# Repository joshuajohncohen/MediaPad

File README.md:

# MediaPad
A macropad for controlling media playback (For Highway)

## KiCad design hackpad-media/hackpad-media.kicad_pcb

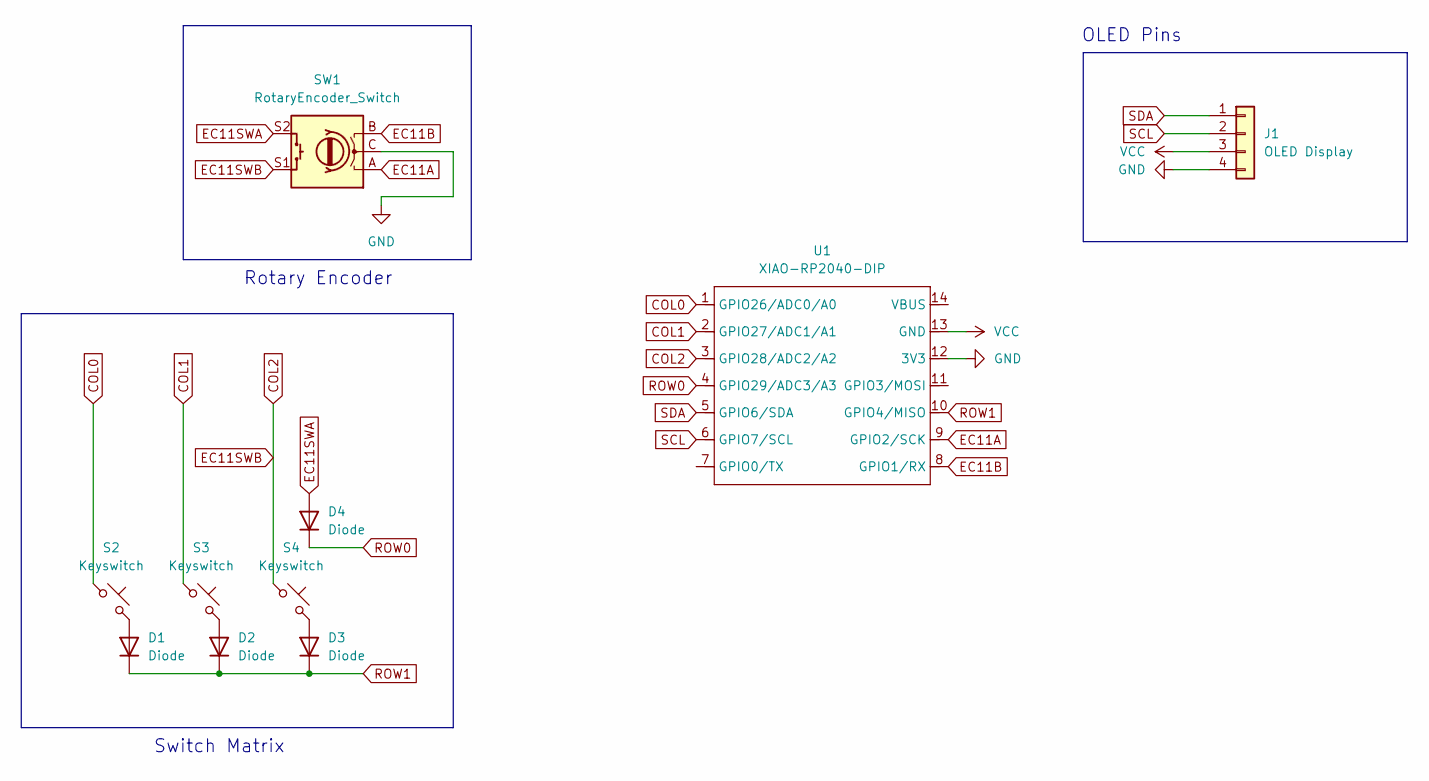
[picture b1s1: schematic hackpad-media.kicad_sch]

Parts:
D1, D2, D3, D4: Diode; Diode_DO-35
J1: OLED Display; OLED_128x32
S2, S3, S4: Keyswitch; MX_PCB_1.00u
SW1: RotaryEncoder_Switch; RotaryEncoder_Alps_EC11E-Switch_Vertical_H20mm_CircularMoun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
U1: XIAO-RP2040-DIP; XIAO-RP2040-DIP-3D

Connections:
COL0: S2.1, U1.1 (GPIO26/ADC0/A0)
COL1: S3.1, U1.2 (GPIO27/ADC1/A1)
COL2: S4.1, SW1.S1, U1.3 (GPIO28/ADC2/A2)
EC11A: SW1.A, U1.9 (GPIO2/SCK)
EC11B: SW1.B, U1.8 (GPIO1/RX)
EC11SWA: D4.2 (A), SW1.S2
GND: J1.4 (GND), SW1.C, U1.12 (3V3)
unnamed: D1.2 (A), S2.2
unnamed: D2.2 (A), S3.2
unnamed: D3.2 (A), S4.2
ROW0: D4.1 (K), U1.4 (GPIO29/ADC3/A3)
ROW1: D1.1 (K), D2.1 (K), D3.1 (K), U1.10 (GPIO4/MISO)
SCL: J1.2 (SCL), U1.6 (GPIO7/SCL)
SDA: J1.1 (SDA), U1.5 (GPIO6/SDA)
VCC: J1.3 (VCC), U1.13 (GND)

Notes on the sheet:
OLED Pins
Rotary Encoder
Switch Matrix

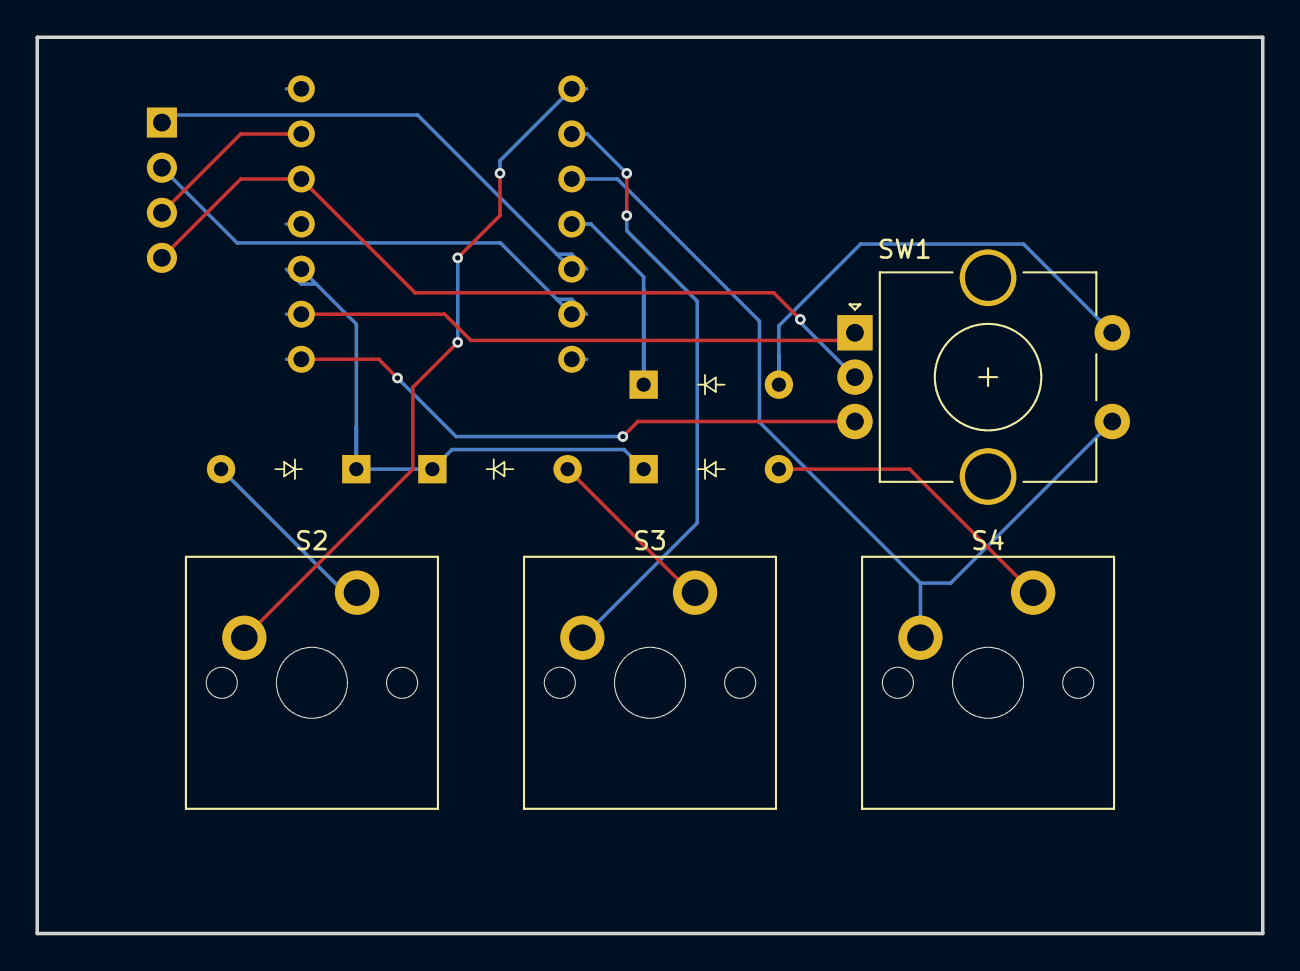
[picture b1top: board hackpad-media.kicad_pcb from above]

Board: 2 copper layers, 69.1 x 50.5 mm, 10 parts (1 on the bottom side), 15 nets.

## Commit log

2025-06-05 Add .gitignore and KiCad files
